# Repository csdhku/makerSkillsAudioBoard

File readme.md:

# Maker skills HW2a Teensy 4.x audio board

[pt8211_2] / AudioOutputPT8211_2
[i2s] / AudioInputI2S

## Bestellen bij JLCPCB

- open production/ map
- https://jlcpcb.com/
- upload teensy_4_makerskills_audio.zip
- PCB opties:
	- PCB Qty: aantal PCB's?
	- Surface Finish: LeadFree HASL of ENIG (duurder)
- PCB assembly:
	- PCBA Type: Standard
	- Assembly Side: Both Sides
- NEXT
- NEXT
- Add BOM File: bom.csv
- Add CPL File: positions.csv
- NEXT
- Check of juiste parts geselecteerd zijn
- NEXT
- Check of oriëntatie en plaatsing van onderdelen klopt
- NEXT
- Bestellen

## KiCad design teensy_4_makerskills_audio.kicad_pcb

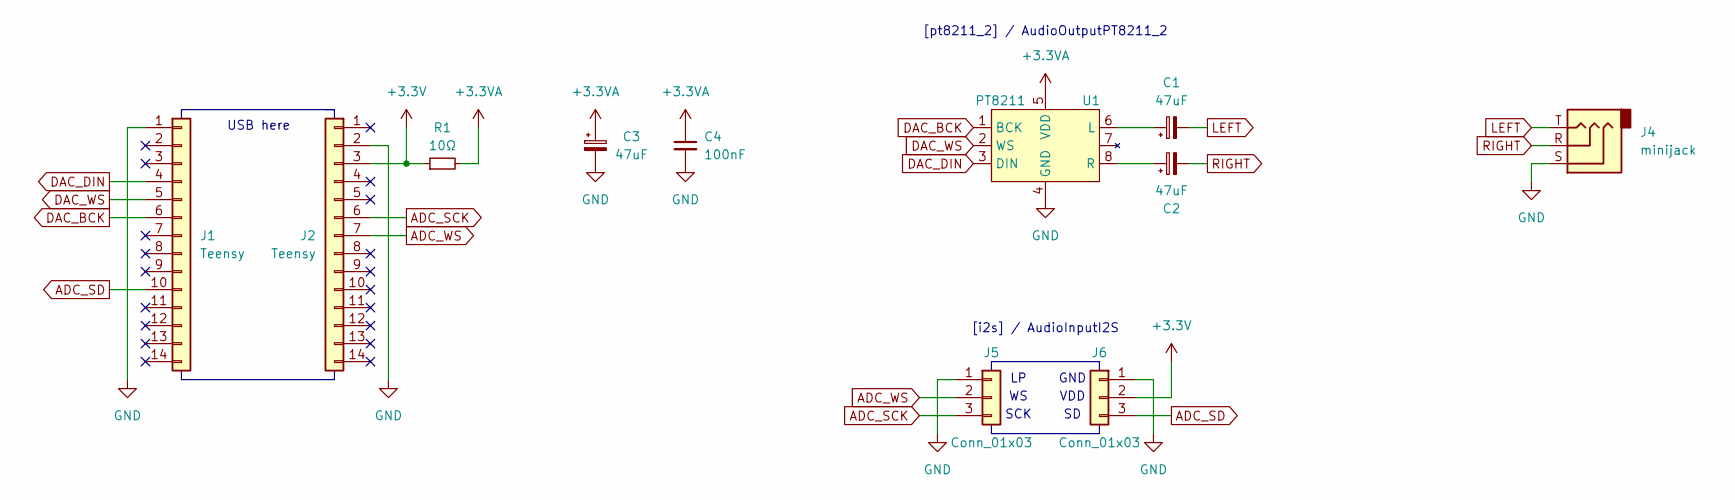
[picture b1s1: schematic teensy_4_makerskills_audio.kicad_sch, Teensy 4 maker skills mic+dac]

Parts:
C1, C2, C3: 47uF; C_1206_3216Metric; LCSC C96123
C4: 100nF; C_0603_1608Metric; LCSC C14663
J1, J2: Teensy; PinHeader_1x14_P2.54mm_Vertical; LCSC C2894937
J4: minijack; Jack_3.5mm_CUI_SJ1-3523N_Horizontal; LCSC C2884991
J5, J6: Conn_01x03; PinSocket_1x03_P2.54mm_Vertical_SMD_Pin1Left; LCSC C42379196
R1: 10Ω; R_0603_1608Metric; LCSC C22859
U1: PT8211; SOIC-8_3.9x4.9mm_P1.27mm; LCSC C5260468

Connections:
+3.3V: J2.3, J6.2, R1.1
+3.3VA: C3.1, C4.1, R1.2, U1.5 (VDD)
ADC_SCK: J2.6, J5.3
ADC_SD: J1.10, J6.3
ADC_WS: J2.7, J5.2
DAC_BCK: J1.6, U1.1 (BCK)
DAC_DIN: J1.4, U1.3 (DIN)
DAC_WS: J1.5, U1.2 (WS)
GND: C3.2, C4.2, J1.1, J2.2, J4.S, J5.1, J6.1, U1.4 (GND)
LEFT: C1.2, J4.T
unnamed: C1.1, U1.6 (L)
unnamed: C2.1, U1.8 (R)
RIGHT: C2.2, J4.R

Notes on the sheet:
USB here
[i2s] / AudioInputI2S
SCK
[pt8211_2] / AudioOutputPT8211_2
GND
VDD

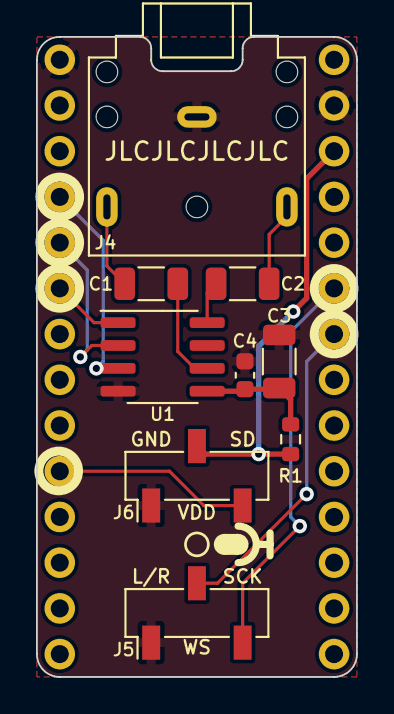
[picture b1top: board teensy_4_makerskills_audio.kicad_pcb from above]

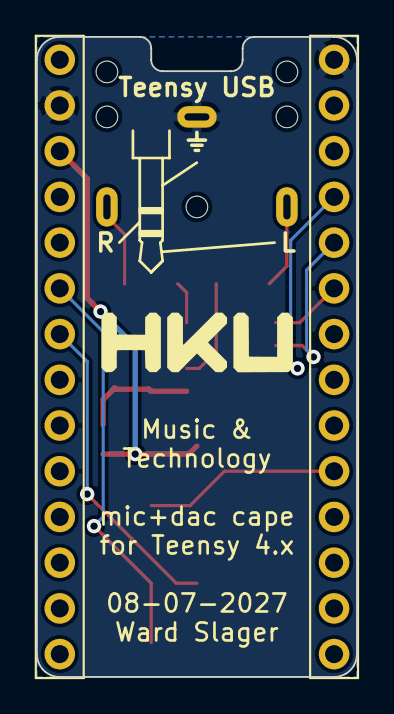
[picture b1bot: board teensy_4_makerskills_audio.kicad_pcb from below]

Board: 2 copper layers, 17.8 x 35.6 mm, 11 parts (2 on the bottom side), 13 nets.

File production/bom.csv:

Designator,Footprint,Quantity,Value,LCSC Part #
"C1, C2, C3",1206,3,47uF,C96123
C4,0603,1,100nF,C14663
"J1, J2",PinHeader_1x14_P2.54mm_Vertical,2,Teensy,C2894937
J4,Jack_3.5mm_CUI_SJ1-3523N_Horizontal,1,minijack,C2884991
"J5, J6",PinSocket_1x03_P2.54mm_Vertical_SMD_Pin1Left,2,Conn_01x03,C42379196
R1,0603,1,10Ω,C22859
U1,SOIC-8_3.9x4.9mm_P1.27mm,1,PT8211,C5260468
